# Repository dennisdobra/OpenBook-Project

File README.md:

# 📖 OpenBook ESP32-C6 – Hardware Overview & Pin Connections

This document describes the **hardware functionality**, **pin mappings**, and **key components** of the OpenBook e-reader, based on the ESP32-C6-WROOM-1-N8 microcontroller.

## 🛠️ Implementation Steps

1. **Schematic Design** – Created in Eagle with all key modules (ESP32-C6, RTC, BME688, etc.).

2. **2D PCB Layout** – Components placed with routing efficiency in mind.

3. **Signal Routing** – Manual routing of SPI, I²C, USB; verified differential pairs.

4. **GND Plane** – Full ground pour on both layers for EMI reduction.

5. **Power Net Classes** – Separate nets for VBAT, VUSB, and 3V3 with wider traces.

6. **Custom Rules** – DRC settings for clearance, trace width, via sizes uploaded.

7. **3D Models** – Designed from datasheets for battery, screen, and connectors.

---

## 🔧 Hardware Overview

### 🧠 Main Controller – ESP32-C6-WROOM-1-N8

- **Architecture**: RISC-V (Single-Core)
- **Wireless**: Wi-Fi 6, Bluetooth 5 LE
- **Operating Voltage**: 3.3V
- **Interfaces**: SPI, I²C, UART, GPIO, USB

---

## 💾 Storage & Display

### 📁 SD Card
- **Interface**: SPI
- **Pins**:
  - CS (SS_SD): `GPIO 4`
  - MOSI: `GPIO 7`
  - MISO: `GPIO 2`
  - SCK: `GPIO 6`

### 🖼️ E-Paper Display
- **Interface**: SPI (shared with SD)
- **Pins**:
  - CS (EPD_CS): `GPIO 10`
  - DC (EPD_DC): `GPIO 5`
  - RESET: `GPIO 23`
  - BUSY: `GPIO 3` *(shared with MISO)*
  - MOSI / SCK: shared with SD

### 💾 External NOR Flash (64MB)
- **Interface**: SPI (shared)
- **Pins**:
  - CS (FLASH_CS): `GPIO 12`
  - Shared: `MOSI`, `MISO`, `SCK`

---

## ⏱️ Timekeeping & Sensors

### 🕒 RTC – DS3231SN
- **Interface**: I²C
- **Pins**:
  - SCL: `GPIO 22`
  - SDA: `GPIO 21`
  - INT: `GPIO 8`
  - 32KHz: `GPIO 1`
  - RESET: `GPIO 18`

### 🌡️ Environmental Sensor – BME688
- **Interface**: I²C (shared with RTC)
- **Supply Voltage**: 3.3V

---

## 🔋 Power Management

### ⚡ Power Supply
- **Input**: USB-C (5V)
- **Output**: 3.3V via LDO regulator
- **Protections**:
  - Reverse polarity diode
  - TVS diodes on USB & SPI lines

### 🔌 Charging Circuit – TP4056
- **Function**: Li-Po battery charging
- **Battery Monitoring**:
  - Gauge via I²C
  - Pins: `GPIO 19` (SCL), `GPIO 20` (SDA)

---

## 🖧 Communication & Interfaces

### 🔌 USB-C Connector
- **Data Pins**:
  - USB_D+: `GPIO 13`
  - USB_D-: `GPIO 12` *(shared with FLASH_CS)*

### 🔗 Qwiic / Stemma QT Connector
- **Interface**: I²C
- **Usage**: Plug-and-play I²C sensors

---

## ⏺️ User Inputs

- **BOOT Button**: `GPIO 9`
- **RESET Button**: connected to EN pin
- **CHANGE Button**: `GPIO 23`

---

## 🛡️ Protection Features

- TVS diodes on:
  - USB data lines
  - SPI lines (SD, Flash, Display)
- Diode-based reverse polarity protection

---

## 🧩 Communication Overview

| Peripheral         | Interface | GPIO Pins Used                       |
|--------------------|-----------|--------------------------------------|
| SD Card            | SPI       | GPIO 2, 4, 6, 7                      |
| E-Paper Display    | SPI       | GPIO 3, 5, 10, 23                    |
| External NOR Flash | SPI       | GPIO 12, shared MOSI/MISO/SCK       |
| RTC + BME688       | I²C       | GPIO 1, 8, 18, 21, 22               |
| Battery Gauge      | I²C       | GPIO 19 (SCL), GPIO 20 (SDA)        |
| USB-C Data         | USB       | GPIO 12 (D-), GPIO 13 (D+)          |
| Buttons            | GPIO      | GPIO 9 (BOOT), GPIO 23 (CHANGE), EN |

---

## 📦 Bill of Materials (BOM)

| Componenta | Link | Preț estimativ |
|------------|------|----------------|
| CHG_LED | [KP-1608SURCK - Kingbright](https://www.snapeda.com/parts/KP-1608SURCK/Kingbright/view-part/?ref=search&t=LED%200603) | 0.15€ |
| SJ1 | [Solder Jumpers](https://grabcad.com/library/solder-jumpers-1) | 0.05€ |
| R3 | [R0402 1% 100K (RC0402FR-07100KL) - YAGEO](https://componentsearchengine.com/part-view/R0402%201%25%20100%20K%20(RC0402FR-07100KL)/YAGEO) | 0.01€ |
| R1_PWRUSB | [R0402 1% 100K (RC0402FR-07100KL) - YAGEO](https://componentsearchengine.com/part-view/R0402%201%25%20100%20K%20(RC0402FR-07100KL)/YAGEO) | 0.01€ |
| C1, C2, C4_USB, C6, C7, C8, C9, C10, C_DELAY | [CC0402MRX5R5BB106 - YAGEO](https://componentsearchengine.com/part-view/CC0402MRX5R5BB106/YAGEO) | 0.10€ (per unitate) |
| C3 | [Link 3D model](https://a360.co/4iZy6AA) | 0.12€ |
| R1_PINH1, R2-PINH1, R_BOOT, R_CHARGE, R_CL1, R_RESET | [R0402 1% 100K (RC0402FR-07100KL) - YAGEO](https://componentsearchengine.com/part-view/R0402%201%25%20100%20K%20(RC0402FR-07100KL)/YAGEO) | 0.01€ (per unitate) |
| R1, R1-PINH, R2-PINH, R4, R5, R6, R7, R8, R9, R10 | [R0402 1% 100K (RC0402FR-07100KL) - YAGEO](https://componentsearchengine.com/part-view/R0402%201%25%20100%20K%20(RC0402FR-07100KL)/YAGEO) | 0.01€ (per unitate) |
| J4 | [Store Comet SRL](https://store.comet.srl.ro/Catalogue/Product/43497/) | 0.35€ |
| R_CAPACITOR | [R0402 1% 100K (RC0402FR-07100KL) - YAGEO](https://componentsearchengine.com/part-view/R0402%201%25%20100%20K%20(RC0402FR-07100KL)/YAGEO) | 0.01€ |
| C5 | [CC0402MRX5R5BB106 - YAGEO](https://componentsearchengine.com/part-view/CC0402MRX5R5BB106/YAGEO) | 0.10€ |
| EPD_C1, EPD_C2, EPD_C5, EPD_C6, EPD_C7, EPD_C8, EPD_C9, EPD_C10, EPD_C11, EPD_C12 | [CC0402MRX5R5BB106 - YAGEO](https://componentsearchengine.com/part-view/CC0402MRX5R5BB106/YAGEO) | 0.10€ (per unitate) |
| R2 | [R0402 1% 100K (RC0402FR-07100KL) - YAGEO](https://componentsearchengine.com/part-view/R0402%201%25%20100%20K%20(RC0402FR-07100KL)/YAGEO) | 0.01€ |
| R1_BAT | [R0402 1% 100K (RC0402FR-07100KL) - YAGEO](https://componentsearchengine.com/part-view/R0402%201%25%20100%20K%20(RC0402FR-07100KL)/YAGEO) | 0.01€ |
| Q1, Q3 | [SI1308EDL-T1-GE3 - Vishay](https://componentsearchengine.com/part-view/SI1308EDL-T1-GE3/Vishay) | 0.45€ (per unitate) |
| R2_BAT | [R0402 1% 100K (RC0402FR-07100KL) - YAGEO](https://componentsearchengine.com/part-view/R0402%201%25%20100%20K%20(RC0402FR-07100KL)/YAGEO) | 0.01€ |
| C1_BAT, C1_BAT1, C1_BAT2, C2_BAT, C5_USB | [CC0402MRX5R5BB106 - YAGEO](https://componentsearchengine.com/part-view/CC0402MRX5R5BB106/YAGEO) | 0.10€ (per unitate) |
| C4 | [CC0402MRX5R5BB106 - YAGEO](https://componentsearchengine.com/part-view/CC0402MRX5R5BB106/YAGEO) | 0.10€ |
| R2-USB, R2-USB1 | [R0402 1% 100K (RC0402FR-07100KL) - YAGEO](https://componentsearchengine.com/part-view/R0402%201%25%20100%20K%20(RC0402FR-07100KL)/YAGEO) | 0.01€ (per unitate) |
| L1 | [744043680 - Wurth Elektronik](https://eu.mouser.com/ProductDetail/Wurth-Elektronik/744043680?qs=PGXP4M47uW6VkZq%252BkzjrHA%3D%3D) | 0.85€ |
| IC1 | [BD5229G-TR - ROHM Semiconductor](https://componentsearchengine.com/part-view/BD5229G-TR/ROHM%20Semiconductor) | 1.20€ |
| BOOT_BUTTON, CHANGE_BUTTON, RESET_BUTTON | [EVQP7L01P - Panasonic](https://www.snapeda.com/parts/EVQP7L01P/Panasonic/view-part/?ref=search&t=evqp7l) | 0.25€ (per unitate) |
| C10_SUPERCAP | [CPH3225A - Seiko Instruments](https://www.snapeda.com/api/url_track_click_mouser/?unipart_id=562593&manufacturer=Seiko%20Instruments&part_name=CPH3225A&search_term=None) | 2.50€ |
| U3 | [DS3231SN - Analog Devices](https://www.snapeda.com/api/url_track_click_mouser/?unipart_id=99048&manufacturer=Analog%20Devices&part_name=DS3231SN#&search_term=None) | 8.95€ |
| U2 | [ESP32-C6-WROOM-1-N8 - Espressif](https://www.snapeda.com/parts/ESP32-C6-WROOM-1-N8/Espressif+Systems/view-part/?ref=eda) | 4.50€ |
| PFMF.050.1 | [B72520T0350K062 - EPCOS-TDK](https://www.mouser.co.uk/ProductDetail/EPCOS-TDK/B72520T0350K062?qs=dEfas%2FXlABIszF52uu7vrg%3D%3D) | 0.65€ |
| D2, D7 | [SD0805S020S1R0 - KYOCERA-AVX](https://eu.mouser.com/ProductDetail/KYOCERA-AVX/SD0805S020S1R0?qs=jCA%252BPfw4LHbpkAoSnwrdjw%3D%3D) | 0.30€ (per unitate) |
| SENSOR2 | [BME680 - Bosch](https://www.snapeda.com/parts/BME680/Bosch/view-part/?welcome=home) | 10.50€ |
| MCP73831 | [MCP73831T-2ACI-OT - Microchip](https://www.digikey.ro/en/products/detail/microchip-technology/MCP73831T-2ACI-OT/964301) | 0.75€ |
| J1 | [XC6220A331MR-G - Torex](https://componentsearchengine.com/part-view/XC6220A331MR-G/Torex) | 1.25€ |
| U4 | [MAX17048G+T10 - Analog Devices](https://www.snapeda.com/api/url_track_click_mouser/?unipart_id=329239&manufacturer=Analog%20Devices&part_name=MAX17048G+T10&search_term=None) | 3.80€ |
| D3, D4, D5 | [MBR0530 - ON Semiconductor](https://www.snapeda.com/api/url_track_click_mouser/?unipart_id=179458&manufacturer=ON%20Semiconductor&part_name=MBR0530&search_term=None) | 0.40€ (per unitate) |
| D6, D8, D9, D10, D11, D12 | [PGB1010603MR - Littelfuse](https://www.snapeda.com/api/url_track_click_mouser/?unipart_id=5659453&manufacturer=Littelfuse%20Inc.&part_name=PGB1010603MR&search_term=None) | 0.30€ (per unitate) |
| J3 | [Model Link - DigiKey](https://www.digikey.ro/en/models/926710) | 1.05€ |
| J2 | [USB4110-GF-A - GCT](https://componentsearchengine.com/part-view/USB4110-GF-A/GCT%20(GLOBAL%20CONNECTOR%20TECHNOLOGY)) | 0.95€ |
| Q2 | [DMG2305UX-7 - Diodes Inc](https://componentsearchengine.com/part-view/DMG2305UX-7/Diodes%20Incorporated) | 0.55€ |
| TP1, TP2, TP3, TP4, TP5, TP6, TP7, TP8, TP9, TP10, TP11, TP12, TP13, TP14, TP15, TP16, TP17 | [Test Points PCB](https://grabcad.com/library/test-points-printed-circuit-board-1) | 0.02€ (per unitate) |
| D1 | [USBLC6-2SC6Y - STMicroelectronics](https://www.snapeda.com/parts/USBLC6-2SC6Y/STMicroelectronics/view-part/?ref=eda) | 0.60€ |
| U1 | [W25Q512JVEIQ - Winbond](https://www.snapeda.com/parts/W25Q512JVEIQ/Winbond+Electronics/view-part/?ref=eda) | 4.20€ |
| IC4 | [XC6220A331MR-G - Torex](https://componentsearchengine.com/part-view/XC6220A331MR-G/Torex) | 1.25€ |

## 📌 Pin Assignments

| ESP32-C6 Pin | Function | Connected To | Description |
|--------------|----------|--------------|-------------|
| 3 | RESET | Reset Button | System hardware reset |
| 4 | SS_SD | SD Card (pin 2) | SPI Slave Select for SD card |
| 6 | SCK | SD Card (pin 5) | SPI Clock signal |
| 7 | MOSI | SD Card (pin 3) | SPI Master Out Slave In |
| 8 | INT_RTC | RTC Module (pin 3) | Interrupt signal from RTC |
| 9 | 32KHz | RTC Module (pin 1) | 32KHz clock signal from RTC |
| 13 | USB_D- | USB-C Connector (pin 3) | USB Data Negative line |
| 14 | USB_D+ | USB-C Connector (pin 1) | USB Data Positive line |
| 15 | IO/BOOT | Boot Button | Boot mode selector button |
| 16 | RTC_RST | RTC Module (pin 4) | RTC reset control |
| 17 | I2C_PW | BME688 Sensor (pins 6, 8, 2) | Power control for environmental sensor |
| 19 | SDA | Multiple I²C devices | I²C Serial Data line (shared) |
| 20 | SCL | Multiple I²C devices | I²C Serial Clock line (shared) |
| 23 | IO/CHANGE | Change Button | Display/Mode change button |
| 27 | MISO | SD Card (pin 7) | SPI Master In Slave Out |

---

# Circuit Block Diagram

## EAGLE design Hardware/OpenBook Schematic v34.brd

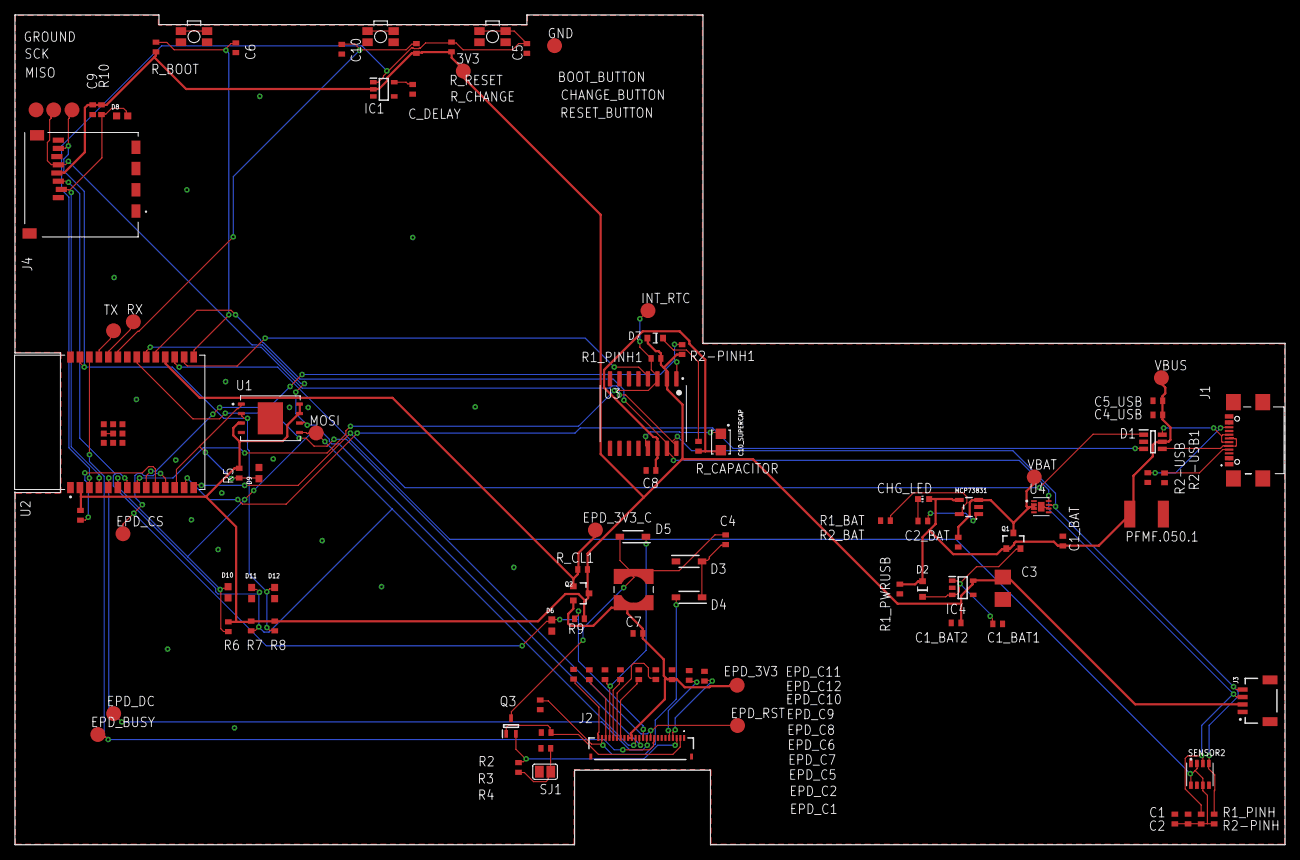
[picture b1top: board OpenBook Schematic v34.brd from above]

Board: 2 copper layers, 170.2 x 111.2 mm, 103 parts (0 on the bottom side), 55 nets.

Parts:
3V3: TPTP20R; TP20R
BOOT_BUTTON: BUTTON_CUSYOMV1; MYBUTTON
C1, C2, C4_USB, C6, C8, C9, C10: 100nF; EAGLE-LTSPICE_C0402
C1_BAT, C1_BAT1, C1_BAT2, C2_BAT, C5_USB: 4.7uF; EAGLE-LTSPICE_C0402
C3: 100uF TANT; RCL_CT3528
C4: 4.7uF/25V; EAGLE-LTSPICE_C0402
C5: 1uF; EAGLE-LTSPICE_C0402
C7: 10uF; EAGLE-LTSPICE_C0402
C10_SUPERCAP: CPH3225A; CAPCP3225X100N
CHANGE_BUTTON: BUTTON_CUSYOMV1; MYBUTTON
CHG_LED: ADAFRUIT_CHIP-LED0603
C_DELAY: 100nF; EAGLE-LTSPICE_C0402
D1: USBLC6-2SC6Y; SOT95P280X145-6N
D2, D7: ESP32_WROVER_AVX---SD0805S020S1R0_AVX_SD0805S020S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; ESP32_WROVER_AVX---SD0805S020S1R0_AVX_SD0805S020S1R0_0
D3, D4, D5: MBR0530; SOD3716X135N
D6, D8, D9, D10, D11, D12: PGB1010603MR; DIOC1608X36N
EPD_3V3, EPD_3V3_C: TPTP20R; TP20R
EPD_BUSY: TPTP20R; TP20R
EPD_C1, EPD_C2, EPD_C6, EPD_C7, EPD_C8, EPD_C9, EPD_C10, EPD_C11, EPD_C12: 1uF/50V; EAGLE-LTSPICE_C0402
EPD_C5: 0.1uF/50V; EAGLE-LTSPICE_C0402
EPD_CS: TPTP20R; TP20R
EPD_DC: TPTP20R; TP20R
EPD_RST: TPTP20R; TP20R
GND: TPTP20R; TP20R
GROUND: TPTP20R; TP20R
IC1: BD5229G-TR; SOT95P280X125-5N
IC4: XC6220A331MR-G; SOT95P280X120-5N
INT_RTC: TPTP20R; TP20R
J1: SAMACSYS_PARTS_USB4110-GF-A; SAMACSYS_PARTS_USB4110GFA
J2: FH34SRJ-24S-0.5SH_99_; FH34SRJ24S05SH99
J3: QWIIC_RIGHT_ANGLE; JST04_1MM_RA
J4: 112A-TAAR-R03_ATTEND; 112ATAARR03ATTEND
L1: 68uH; IND_4828-WE-TPC_WRE
MCP73831: ESP32_WROVER_SPARKFUN-IC-POWER_MCP73831; ESP32_WROVER_SPARKFUN-IC-POWER_SOT23-5
MISO: TPTP20R; TP20R
MOSI: TPTP20R; TP20R
PFMF.050.1: ESP32C6_VARISTORCN1812; ESP32C6_VARISTOR_CT/CN1812
Q1, Q2: 20V/4.2A/52mΩ/1.4W; ESP32_WROVER_SPARKFUN-DISCRETESEMI_SOT23-3
Q3: SI1308EDL-T1-GE3; SOT65P210X110-3N
R1, R1_PINH, R1_PINH1, R2-PINH, R2-PINH1, R4, R5, R6, R7, R8, R9, R10: 10K; ESP32_WROVER_EAGLE-LTSPICE_R0402
R1_BAT: 200; ESP32_WROVER_EAGLE-LTSPICE_R0402
R1_PWRUSB: 100k; ESP32_WROVER_EAGLE-LTSPICE_R0402
R2: 2.2; ESP32_WROVER_EAGLE-LTSPICE_R0402
R2-USB, R2-USB1: 5k1; ESP32_WROVER_EAGLE-LTSPICE_R0402
R2_BAT: 2K; ESP32_WROVER_EAGLE-LTSPICE_R0402
R3: 0.47; ESP32_WROVER_EAGLE-LTSPICE_R0402
RESET_BUTTON: BUTTON_CUSYOMV1; MYBUTTON
RX: TPTP20R; TP20R
R_BOOT: 10K; ESP32_WROVER_EAGLE-LTSPICE_R0402
R_CAPACITOR: 15; ESP32_WROVER_EAGLE-LTSPICE_R0402
R_CHANGE: 10K; ESP32_WROVER_EAGLE-LTSPICE_R0402
R_CL1: 10K; ESP32_WROVER_EAGLE-LTSPICE_R0402
R_RESET: 10K; ESP32_WROVER_EAGLE-LTSPICE_R0402
SCK: TPTP20R; TP20R
SENSOR2: ESP32_WROVER_BME680_BME680; ESP32_WROVER_BME680_PSON80P300X300X100-8N
SJ1: SJ
TX: TPTP20R; TP20R
U1: W25Q512JVEIQ; SON127P600X800X80-9N
U2: ESP32-C6-WROOM-1-N8; XCVR_ESP32-C6-WROOM-1-N8
U3: DS3231SN#; SOIC127P1032X265-16N
U4: MAX17048G+T10; SON50P200X200X80-9N
VBAT: TPTP20R; TP20R
VBUS: TPTP20R; TP20R

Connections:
3V3: 3V3.TP, C1_BAT2.1, C3.+, C9.1, D7.2, IC1.2, IC4.5, J3.2, J4.P4, Q2.3, R1.2, R1_PINH1.2, R2-PINH1.2, R5.2, R6.2, R7.2, R8.2, R9.2, R10.2, R_BOOT.2, R_CHANGE.2, R_CL1.2, R_RESET.2, U1.3, U1.7, U1.8, U2.2, U3.2
32KHZ: R2-PINH1.1, U2.9, U3.1
DN: D1.4, J1.A7, J1.B7
DP: D1.6, J1.A6, J1.B6
EPD_3V3: C7.1, EPD_3V3.TP, EPD_C5.2, J2.15, J2.16, L1.2, Q2.2
EPD_3V3_C: EPD_3V3_C.TP, Q2.1, R_CL1.1, U2.18
EPD_BUSY: EPD_BUSY.TP, J2.9, U2.26
EPD_CS: D6.2, EPD_CS.TP, J2.12, R9.1, U2.11
EPD_DC: EPD_DC.TP, J2.11, U2.5
EPD_RST: EPD_RST.TP, J2.10, U2.21
FLASH_CS: D9.2, R5.1, U1.1, U2.12
GDR: J2.2, Q3.1, R4.2
GND: BOOT_BUTTON.1, BOOT_BUTTON.2, C1.2, C1_BAT.2, C1_BAT1.2, C1_BAT2.2, C2.2, C2_BAT.2, C3.-, C4_USB.2, C5.2, C5_USB.2, C6.2, C7.2, C8.2, C9.2, C10.2, C10_SUPERCAP.1, CHANGE_BUTTON.1, CHANGE_BUTTON.2, C_DELAY.2, D1.2, D3.1, D6.1, D8.1, D9.1, D10.1, D11.1, D12.1, EPD_C1.1, EPD_C2.1, EPD_C5.1, EPD_C6.1, EPD_C7.1, EPD_C8.1, EPD_C9.1, EPD_C10.1, EPD_C11.1, EPD_C12.1, GND.TP, GROUND.TP, IC1.3, IC4.2, J1.A1, J1.A12, J1.B1, J1.B12, J1.MP1, J1.MP2, J1.MP3, J1.MP4, J2.8, J2.17, J2.MP1, J2.MP2, J3.1, J4.G1, J4.G2, J4.G3, J4.G4, J4.P6, MCP73831.2, R1_PWRUSB.1, R2.1, R2-USB.2, R2-USB1.1, R2_BAT.1, R4.1, RESET_BUTTON.1, RESET_BUTTON.2, SENSOR2.1, SENSOR2.5, SENSOR2.7, SJ1.1, U1.4, U1.9, U2.1, U2.28, U2.29_1, U2.29_2, U2.29_3, U2.29_4, U2.29_5, U2.29_6, U2.29_7, U2.29_8, U2.29_9, U3.13, U4.1, U4.4, U4.6, U4.9
GPIO8: R1.1, U2.10
I2C_PW: C1.1, C2.1, R1_PINH.2, R2-PINH.2, SENSOR2.2, SENSOR2.6, SENSOR2.8, U2.17
INT_RTC: INT_RTC.TP, R1_PINH1.1, U2.8, U3.3
IO/BOOT: BOOT_BUTTON.3, BOOT_BUTTON.4, C6.1, R_BOOT.1, U2.15
IO/CHANGE: C10.1, CHANGE_BUTTON.3, CHANGE_BUTTON.4, R_CHANGE.1, U2.23
MISO: D12.2, J4.P7, MISO.TP, R8.1, U1.2, U2.27
MOSI: D11.2, J2.14, J4.P3, MOSI.TP, R7.1, U1.5, U2.7
unnamed: MCP73831.1, R1_BAT.2
unnamed: C1_BAT1.1, D2.1, IC4.1, IC4.3, Q1.2
unnamed: CHG_LED.C, R1_BAT.1
unnamed: MCP73831.5, R2_BAT.2
unnamed: D7.1, R_CAPACITOR.1
unnamed: C_DELAY.1, IC1.5
unnamed: J1.A5, R2-USB1.2
unnamed: C4.1, D3.2, D4.1
unnamed: EPD_C1.2, J2.4
unnamed: J1.B5, R2-USB.1
unnamed: EPD_C2.2, J2.5
unnamed: EPD_C10.2, J2.22
unnamed: EPD_C12.2, J2.24
unnamed: EPD_C7.2, J2.19
unnamed: EPD_C8.2, J2.20
unnamed: EPD_C6.2, J2.18
PREVGH: D5.1, EPD_C9.2, J2.21
PREVGL: D4.2, EPD_C11.2, J2.23
RESE: J2.3, Q3.2, R3.2
RESE': R2.2, R3.1, SJ1.2
RESET: C5.1, IC1.1, RESET_BUTTON.3, RESET_BUTTON.4, R_RESET.1, U2.3
RTC_RST: U2.16, U3.4
RX: RX.TP, U2.24
SCK: D10.2, J2.13, J4.P5, R6.1, SCK.TP, U1.6, U2.6
SCL: J3.4, R2-PINH.1, SENSOR2.4, U2.20, U3.16, U4.7
SDA: J3.3, R1_PINH.1, SENSOR2.3, U2.19, U3.15, U4.8
SRC: C4.2, D5.2, L1.1, Q3.3
SS_SD: D8.2, J4.P2, R10.1, U2.4
TX: TX.TP, U2.25
USB_D+: D1.1, U2.14
USB_D-: D1.3, U2.13
VBAT: C2_BAT.1, MCP73831.3, Q1.3, U4.2, U4.3, VBAT.TP
VBUS: C1_BAT.1, C4_USB.1, C5_USB.1, CHG_LED.A, D1.5, D2.2, MCP73831.4, PFMF.050.1.2, Q1.1, R1_PWRUSB.2, VBUS.TP
VRTC: C8.1, C10_SUPERCAP.2, R_CAPACITOR.2, U3.14
VUSB: J1.A4, J1.A9, J1.B4, J1.B9, PFMF.050.1.1

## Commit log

2025-04-06 OpenBook Project completed
2025-04-06 Readme
2025-04-06 added images
2025-04-06 modified README
2025-04-06 removed .vscode file
2025-04-06 Create LICENSE
2025-04-06 update BOM and PnP files
2025-04-14 corrected the raised issues

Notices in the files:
parts and their libraries:
COPYRIGHT: Copyright (C) 2024 Ultra Librarian. All rights reserved.
